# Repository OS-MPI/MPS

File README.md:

# The Magnetic Particle Spectroscopy (MPS) device
# [Link to the wiki](https://github.com/OS-MPI/MPS/wiki)
# [Link to the Main OS-MPI Page](https://os-mpi.github.io/)

## Motivation and Introduction

The system we are calling the MPS device is a low cost, and fairly simple to manufacture project which more generally speaking is a platform designed around understanding magnetic characteristics of superparamagentic iron oxide nanoparticles (SPIONs). The motivation was to condense the numerous existing systems into a singlular platform capable of providing insights into the nanoparticles irrespective of the specific goal of the lab. With that in mind, calling our platform an "MPS" system is rather imprecise; while one mode is traditional "spectroscopy" the device is designed to be flexible and able to perform relaxometry measurements as well as magnetometry, yet in order to give the project an easy-to-find, descriptive name, we settled on the "magnetic particle spectroscopy" system. 

## State of the project

In the current state (of March 2024) we have the system working in all [primary operational modes](https://github.com/OS-MPI/MPS/wiki/Modes-of-operation). It is capable of sensitively detecting SPIONs to the ng Fe level, quantifying the magnetization spectra, tracing the hysteresis loops, etc. 

The primary focus now is improving the documentation.

## System overview

Broadly speaking, there are four principle hardware components, the three coils (drive, receive, and bias) and the sample positioner. The drive coils produce magnetic fields (typ. 10 mT) which cause the SPIONs within the bore to go into and out of saturation at 23.8 kHz. This changing magnetism induces a voltage in the receive coils. The bias coils allow for the quasistatic operating point of the SPIONs to be modulated by generating low frequency (~10 Hz) fields up to about 50 mT.

### Drive/Transmit system
The drive system consists of the drive coils as well as the amplifier and filter. 

The drive coil is seen in the photograph above (the larger coil with four sub-sections). All of the four winding sections are in the same handedness. See the Wiki for further details. 

In this photograph, we utilize an in-house made Litz wire (18 strands of 28 AWG magnet wire), although other Litz wires may work similarly well. Previously a commercial Litz wire with 115 strands of 36AWG was used, but because of the plastic sleeve over the wires, they could not be easily stabilized with epoxy. 

The drive filter serves to purify and the waveform produced by the amplifier. Most amplifiers produce about 0.1% (or worse) total harmonic distortion, so without this filter those amplifier-generated distortions will dominate the noise floor. That being said, its among the most challenging components to manufacture, so its worth discussing which components are essential, and which are more or less optional. Refering to the schematic below, the two most important sections are the tuning/matching capacitors (C1 and C2), and the transformer (LPri and LSec). The tuning capacitors form a resonant circuit with Ldrive (the drive coil's equivalent load). This can be seen if you notice the loop formed by C1 C2 and LDrive is resonant. The choice of values for C1 and C2 is to make the equivalent impedance 8 ohms or so. The transformer should be a ferrite such as N87 and be designed such that the core flux is well below saturation (~20x lower, so 20ish mT). The purpose is to mitigate common-mode noise and provide isolation/break any ground loops. The other filter components can be "dropped in" later without disturbing the overall circuit. But these additional filtering components are both the most challenging to build, and less necessary. 

Many different drive amplifiers can be used. We have used both linear and switch-mode amplifiers with success. For a basic system, the AIYIMA A07 can be used, or other amplifiers based on the TPA3255 will likely be good choices. For example Nobsound G2 pro is also likely good and is pre-configured to be in PBTL mode. That IC from Texas Instruments has excellent performance given the cost and high switching frequency. The AE Techron 7224 is considerably more expensive, but produces a much higher fidelity waveform and has far more power available.

### Receive system

The receive system consists of the gradiometer receive coils, the filter, matching transformer, and preamplifier. The receive coil is a simple gradiometer to mitigate the net voltage induced from the changing magnetic drive fields (60-80 dBc attenuation of the voltage is a reasonable target). The filter reduces the amplitude of the signal at the drive frequency, but doesnt fully remove it. The matching transformer steps up the voltage produced by the receive coil (post filter) to improve the noise performance of the system. The transformer also provides isolation and common-mode supression, which help signal fidelity. The preamplifier amplifies the signal to a level more usable by the data acquisition hardware. In our case, we digitize the signals with a National Instruments NI PXIe 6363 and 6361. 

### Bias system

The bias system applies a low frequency (~10Hz), high amplitude waveform to probe the magnetization response at different quasistatic operating points. "Quasistatic" is emphasized here just because we utilize the assumption that this frequency is so low relaxation effects are negligible.

The system was initially designed to allow for even very small SPIONs (e.g. 5nm) to be probed out toward saturation, so many turns were added and cooling spaces were added to allow air to pass between the windings. With this design, passive convection is sufficient for normal operation at 50 mT peak. For up to 100 mT peak, lower duty cycles, or forced air should be used. 

This coil can be neglected if only hysteresis loop tracing or spectroscopy modes will be used. In that case, the diameter of the shielding tube should be increased to about 50-60 mm diameter. 

### Sample positioner

An automatic sample positioner is used to allow for consistent placement of the SPIONs as well as having the sample move in and out repeatedly to allow for multiple baselines to acquired. 

### Software

The software is written with LabVIEW 2021. Labview is not backwards compatible, so it must be operated with version 2021 or newer. 

With any issues regarding the project or missing files/documentation, [please reach out to the authors of this project here](https://github.com/OS-MPI/MPS/wiki/Contact-Us).

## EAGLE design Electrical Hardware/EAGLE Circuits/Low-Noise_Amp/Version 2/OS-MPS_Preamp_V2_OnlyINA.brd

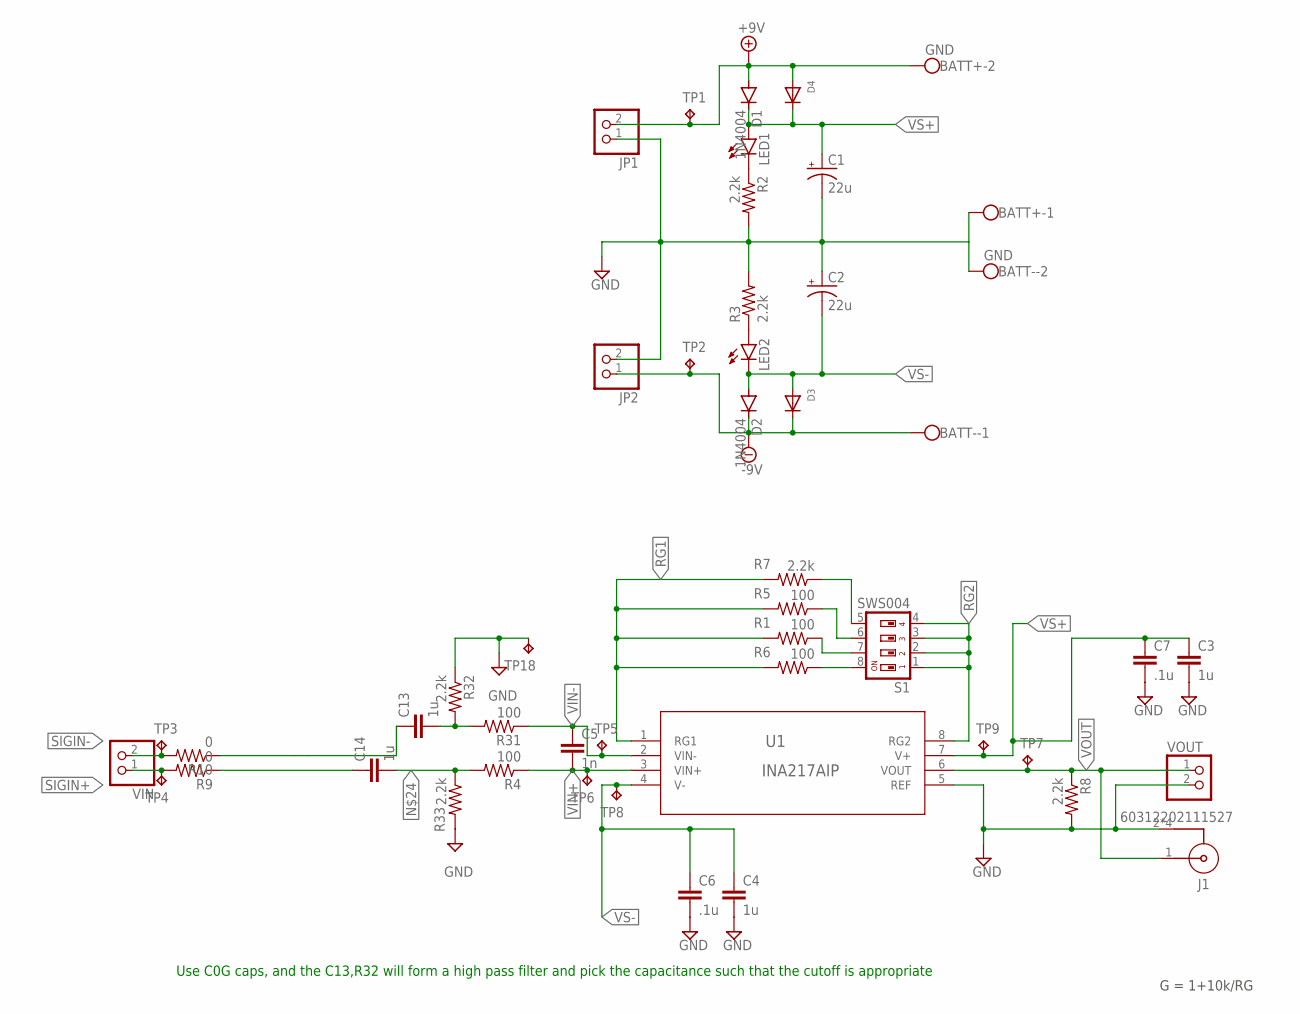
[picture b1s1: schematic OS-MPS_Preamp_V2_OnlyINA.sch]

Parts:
BATT+: GND; W237-102
BATT-: GND; W237-102
C1, C2: 22u; TT2D6
C3, C4, C13, C14: 1u; C1206
C5: 1n; C1206
C6, C7: .1u; C1206
D1, D2: 1N4004; DO41-10
D3, D4: DIODESOD-123; SOD-123
J1: 60312202111527
JP1, JP2: PINHD-1X2; 1X02
LED1, LED2: LEDSML0805; SML0805
R1, R4, R5, R6, R31: 100; R0805
R2, R3, R7, R8, R32, R33: 2.2k; R0805
R9, R10: 0; R0805
S1: SWS004; SMS-004
TP1, TP2: TPB2,54; B2,54
TP3, TP4, TP5, TP6, TP7, TP8, TP9, TP18: TPTP20SQ; TP20SQ
U1: INA217AIP; P8
VIN: PINHD-1X2; 1X02
VOUT: PINHD-1X2; 1X02

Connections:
+9V: BATT+.2, D1.A, D4.A, JP1.2, TP1.TP
-9V: BATT-.1, D2.C, D3.C, JP2.1, TP2.TP
GND: BATT+.1, BATT-.2, C1.-, C2.+, C3.2, C4.2, C6.2, C7.2, J1.2, J1.3 (2), J1.4 (2), J1.5 (2), JP1.1, JP2.2, R2.2, R3.2, R8.2, R32.1, R33.2, TP18.TP, U1.5 (REF), VOUT.2
unnamed: LED1.C, R2.1
unnamed: R5.1, S1.6
unnamed: R1.1, S1.7
unnamed: R6.1, S1.8
unnamed: R7.1, S1.5
unnamed: LED2.A, R3.1
unnamed: C13.1, R10.1
unnamed: C14.2, R4.2, R33.1
unnamed: C13.2, R31.2, R32.2
RG1: R1.2, R5.2, R6.2, R7.2, U1.1 (RG1)
RG2: S1.1, S1.2, S1.3, S1.4, U1.8 (RG2)
SIGIN+: R9.2, TP4.TP, VIN.1
SIGIN-: R10.2, TP3.TP, VIN.2
VIN+: C5.2, R4.1, TP6.TP, U1.3 (VIN+)
VIN+_1: C14.1, R9.1
VIN-: C5.1, R31.1, TP5.TP, U1.2 (VIN-)
VOUT: J1.1, R8.1, TP7.TP, U1.6 (VOUT), VOUT.1
VS+: C1.+, C3.1, C7.1, D1.C, D4.C, LED1.A, TP9.TP, U1.7 (V+)
VS-: C2.-, C4.1, C6.1, D2.A, D3.A, LED2.C, TP8.TP, U1.4 (V-)

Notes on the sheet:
Use C0G caps, and the C13,R32 will form a high pass filter and pick the capacitance such that the cutoff is appropriate
G = 1+10k/RG

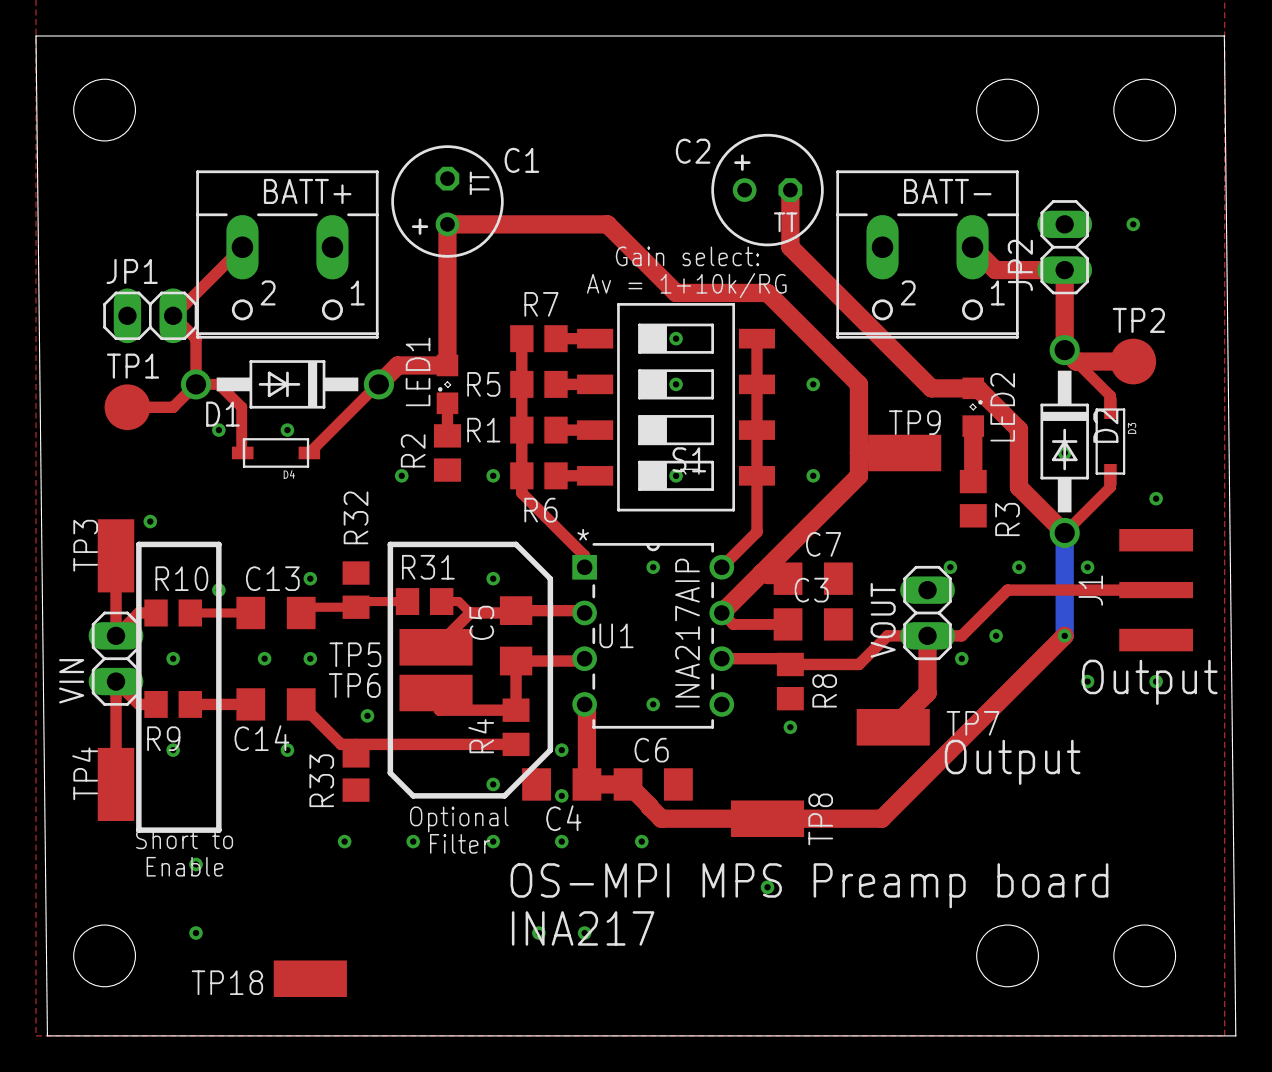
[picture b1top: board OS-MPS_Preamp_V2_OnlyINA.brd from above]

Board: 2 copper layers, 66.7 x 55.6 mm, 47 parts (0 on the bottom side), 22 nets.

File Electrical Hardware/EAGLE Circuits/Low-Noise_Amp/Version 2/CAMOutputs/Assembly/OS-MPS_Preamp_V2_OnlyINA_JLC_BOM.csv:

Comment,Designator,Package,LCSC Part,,,,,,,,,,,,,,,,,,,,,,2
2.2k,"R2,R3,R7,R8,R32,R33",R0805,C17520,,,,,,,,,,,,,,,,,,,,,,
0,"R9,R10",R0805,C17477,,,,,,,,,,,,,,,,,,,,,,
,"LED1,LED2",SML0805,C84256,,,,,,,,,,,,,,,,,,,,,,
100,"R1,R4,R5,R6,R31",R0805,C17408,,,,,,,,,,,,,,,,,,,,,,
,"D3,D4",SOD-123,C64898,,,,,,,,,,,,,,,,,,,,,,
100n,"C6,C7",C1206,C24497,,,,,,,,,,,,,,,,,,,,,,
1n,C5,C1206,C35216,,,,,,,,,,,,,,,,,,,,,,
SWS004,S1,SMS-004,C3693,,,,,,,,,,,,,,,,,,,,,,
1u,"C3,C4,C13,C14",C1206,C1848,,,,,,,,,,,,,,,,,,,,,,

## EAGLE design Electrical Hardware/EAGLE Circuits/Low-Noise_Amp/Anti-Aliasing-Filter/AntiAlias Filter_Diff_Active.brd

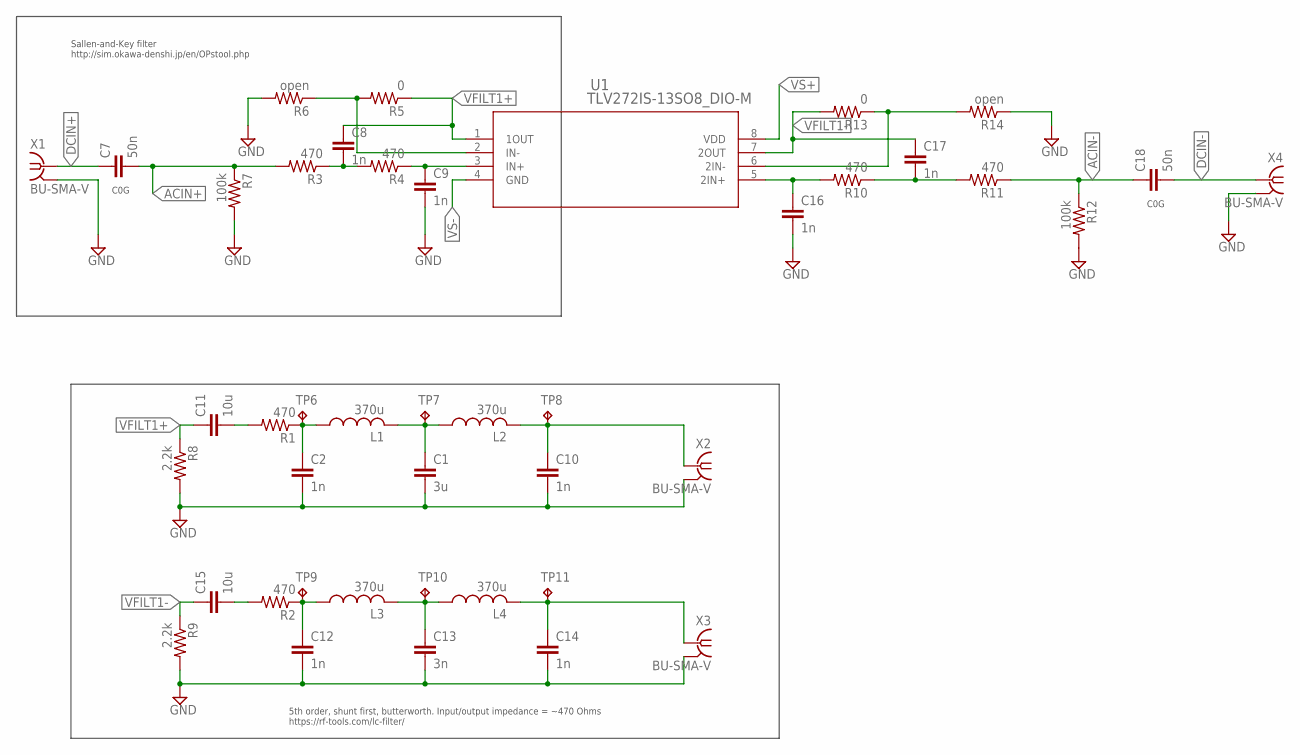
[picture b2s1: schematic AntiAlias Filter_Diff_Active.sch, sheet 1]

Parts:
C1: 3u; C1206
C2, C8, C9, C10, C12, C14, C16, C17: 1n; C1206
C7, C18: 50n; C1210
C11, C15: 10u; C1210
C13: 3n; C1206
L1, L2, L3, L4: 370u; L1812
R1, R2, R3, R4, R10, R11: 470; R1206
R5, R13: 0; R1206
R6, R14: open; R1206
R7, R12: 100k; R1206
R8, R9: 2.2k; R1206
TP6, TP7, TP8, TP9, TP10, TP11: TPTP20SQ; TP20SQ
U1: TLV272IS-13SO8_DIO-M; SO8_DIO-M
X1, X2, X3, X4: BU-SMA-V

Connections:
ACIN+: C7.2, R3.2, R7.1
ACIN-: C18.1, R11.1, R12.1
DCIN+: C7.1, X1.1
DCIN-: C18.2, X4.1
GND: C1.2, C2.2, C9.2, C10.2, C12.2, C13.2, C14.2, C16.2, R6.2, R7.2, R8.2, R9.2, R12.2, R14.1, X1.2, X1.3 (2), X1.4 (2), X1.5 (2), X2.2, X2.3 (2), X2.4 (2), X2.5 (2), X3.2, X3.3 (2), X3.4 (2), X3.5 (2), X4.2, X4.3 (2), X4.4 (2), X4.5 (2); also elsewhere on the board
unnamed: C2.1, L1.1, R1.1, TP6.TP
unnamed: C1.1, L1.2, L2.1, TP7.TP
unnamed: C11.2, R1.2
unnamed: C10.1, L2.2, TP8.TP, X2.1
unnamed: C14.1, L4.2, TP11.TP, X3.1
unnamed: C9.1, R4.1, U1.3 (IN+)
unnamed: C8.2, R3.1, R4.2
unnamed: R5.2, R6.1, U1.2 (IN-)
unnamed: C12.1, L3.1, R2.1, TP9.TP
unnamed: C13.1, L3.2, L4.1, TP10.TP
unnamed: C15.2, R2.2
unnamed: C17.2, R10.1, R11.2
unnamed: C16.1, R10.2, U1.5 (2IN+)
unnamed: R13.1, R14.2, U1.6 (2IN-)
VFILT1+: C8.1, C11.1, R5.1, R8.1, U1.1 (1OUT)
VFILT1-: C15.1, C17.1, R9.1, R13.2, U1.7 (2OUT)
VS+: U1.8 (VDD); also elsewhere on the board
VS-: U1.4 (GND); also elsewhere on the board

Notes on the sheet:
5th order, shunt first, butterworth. Input/output impedance = ~470 Ohms https://rf-tools.com/lc-filter/
Sallen-and-Key filter http://sim.okawa-denshi.jp/en/OPstool.php
C0G

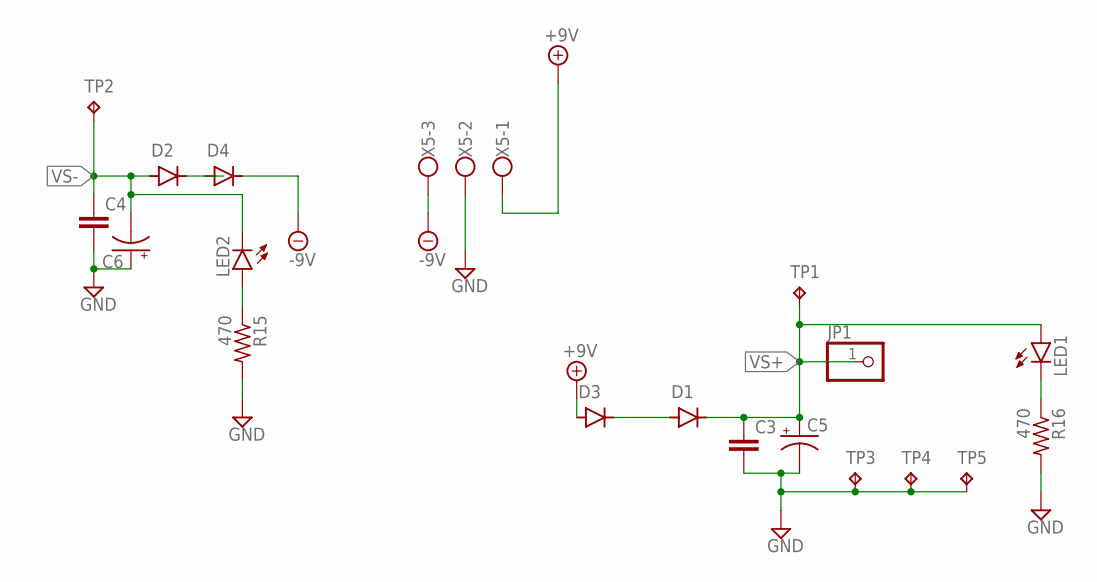
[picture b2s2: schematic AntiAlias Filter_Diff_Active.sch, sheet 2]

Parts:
C3, C4: C-EUC1206; C1206
C5, C6: CPOL-USE2.5-5; E2,5-5
D1, D2, D3, D4: DIODE-SMB; SMB
JP1: PINHD-1X1; 1X01
LED1, LED2: LEDCHIPLED_1206; CHIPLED_1206
R15, R16: 470; R1206
TP1, TP2, TP3, TP4, TP5: TPTP20SQ; TP20SQ
X5: W237-103

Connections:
+9V: D3.A, X5.1; also elsewhere on the board
-9V: D4.C, X5.3; also elsewhere on the board
GND: C3.2, C4.2, C5.-, C6.+, R15.2, R16.2, TP3.TP, TP4.TP, TP5.TP, X5.2; also elsewhere on the board
unnamed: LED2.A, R15.1
unnamed: LED1.C, R16.1
unnamed: D1.A, D3.C
unnamed: D2.C, D4.A
VS+: C3.1, C5.+, D1.C, JP1.1, LED1.A, TP1.TP; also elsewhere on the board
VS-: C4.1, C6.-, D2.A, LED2.C, TP2.TP; also elsewhere on the board

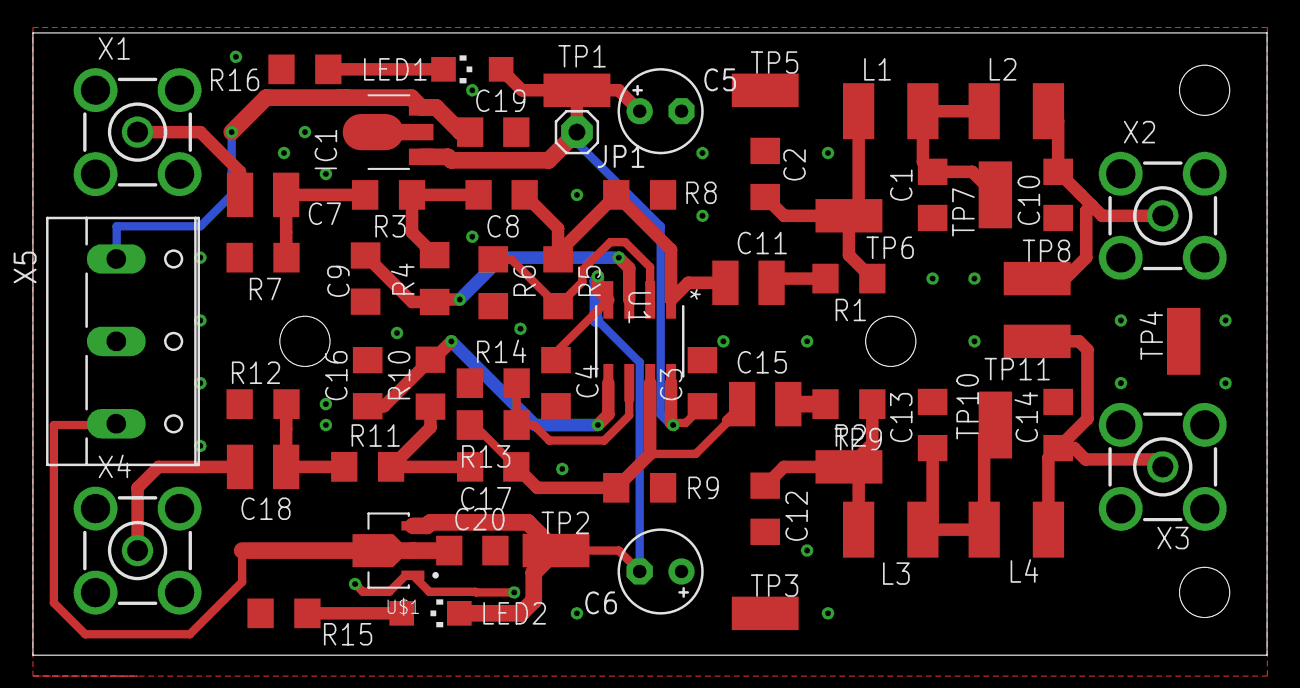
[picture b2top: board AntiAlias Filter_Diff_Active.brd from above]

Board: 2 copper layers, 74.9 x 37.8 mm, 62 parts (0 on the bottom side), 27 nets.

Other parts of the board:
C19, C20: C1206
IC1: 78L05F; SOT89
U$1: 79LXX; VREG_L78L12ABUTR

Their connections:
+9V: C19.1, IC1.3; also elsewhere on the board
-9V: C20.1, U$1.2; also elsewhere on the board
GND: C19.2, C20.2, IC1.2, IC1.2@1, U$1.1; also elsewhere on the board
VS+: IC1.1; also elsewhere on the board
VS-: U$1.3; also elsewhere on the board

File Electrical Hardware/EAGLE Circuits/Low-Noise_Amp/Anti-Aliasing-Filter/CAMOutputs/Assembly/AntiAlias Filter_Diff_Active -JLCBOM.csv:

Value,Designator,Package,LCSC Part
,"LED1, LED2",CHIPLED_1206,
10u,"C3, C4, C19, C20",C1206,
0,"R5, R13",R1206,
100k,"R7, R12",R1206,
10u,,C1210,
1n,"C2, C8, C9, C10, C12, C14, C16, C17",C1206,
2.2k,"R8, R9",R1206,
270u,"L1, L2, L3, L4",L1812,C394138
3n,"C1,C13",C1206,C141013
470,"R1, R2, R3, R4, R10, R11, R15, R16",R1206,
47n,"C7, C18,C11, C15",C1210,C342651
78L05F,IC1,SOT89,C181132
79LXX,U$1,SOT89,C122849
TLC082IDR,U1,SO8_DIO-M,C7710

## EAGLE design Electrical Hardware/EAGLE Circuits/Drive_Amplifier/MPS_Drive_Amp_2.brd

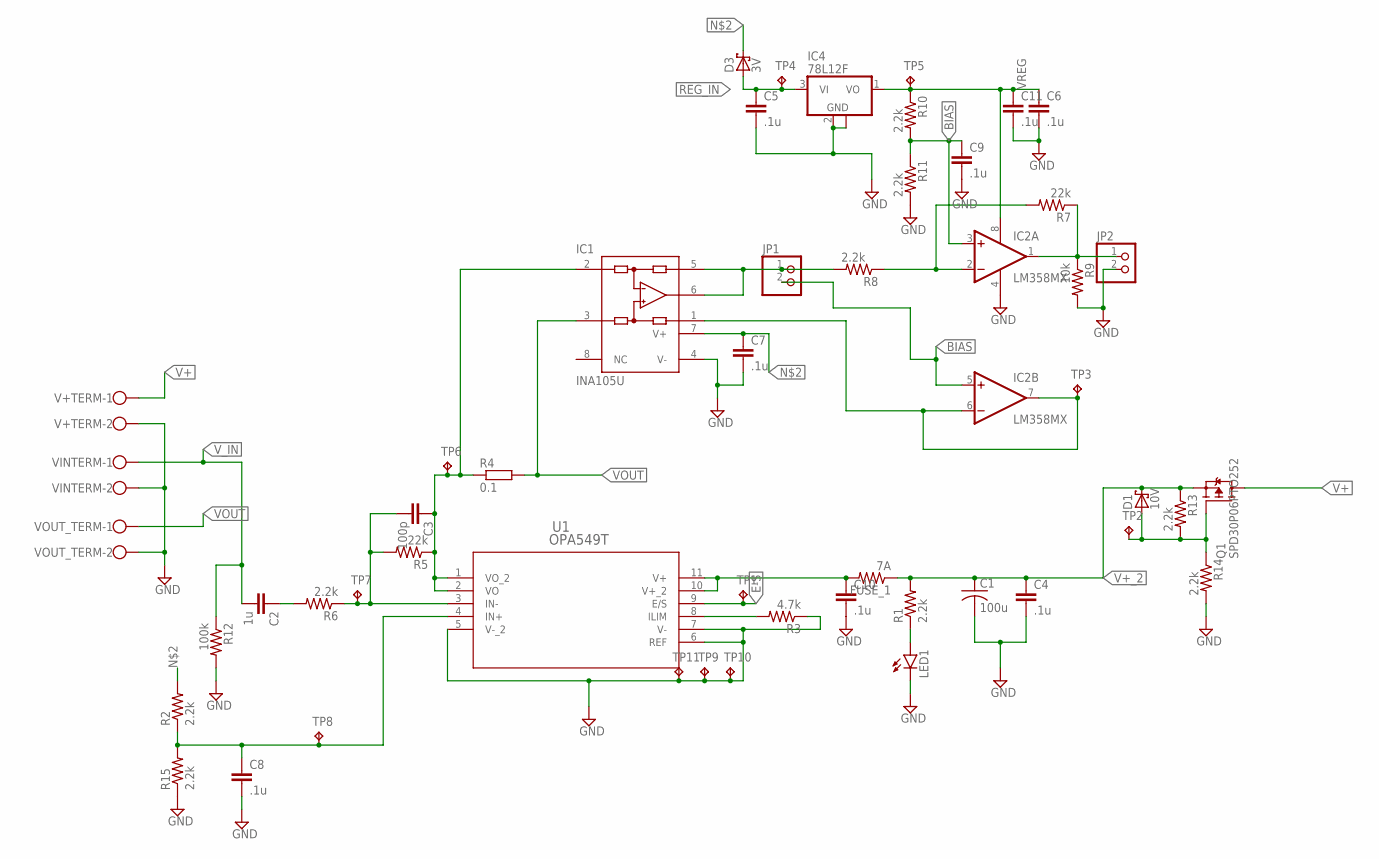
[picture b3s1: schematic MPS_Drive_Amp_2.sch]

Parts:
C1: 100u; C050-025X075
C2: 1u; C1206
C3: 100p; C1206
C4, C5, C6, C7, C8, C9, C10, C11: .1u; C1206
D1: 10V; DO35-7
D3: 3V; DO35-7
FUSE_1: 7A; R1206
IC1: INA105U; SO08
IC2: LM358MX; SO08
IC4: 78L12F; SOT89
JP1, JP2: PINHD-1X2; 1X02
LED1: LEDCHIPLED_0805; CHIPLED_0805
Q1: SPD30P06PTO252; TO252
R1, R2, R6, R8, R10, R11, R13, R14, R15: 2.2k; R1206
R3: 4.7k; R1206
R4: 0.1; VTA52
R5, R7: 22k; R1206
R9: 10k; R1206
R12: 100k; R1206
TP1, TP2, TP3, TP4, TP5, TP6, TP7, TP8, TP9, TP10, TP11: TPTP20SQ; TP20SQ
U1: OPA549T; KV11
V+TERM: W237-102
VINTERM: W237-102
VOUT_TERM: W237-102

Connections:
BIAS: C9.1, IC2.3 (+IN), IC2.5 (+IN), JP1.2, R10.2, R11.1
E-S: TP1.TP, U1.9 (E/S)
GND: C1.2, C4.2, C5.2, C6.2, C7.2, C8.2, C9.2, C10.2, C11.2, IC1.4 (V-), IC2.4 (V-), IC4.2 (GND), IC4.2@1 (GND), JP2.2, LED1.C, R3.1, R9.2, R11.2, R12.2, R14.2, R15.1, TP9.TP, TP10.TP, TP11.TP, U1.5 (V-_2), U1.6 (REF), U1.7 (V-), V+TERM.2, VINTERM.2, VOUT_TERM.2
unnamed: C3.1, IC1.2 (-IN), R4.1, R5.1, TP6.TP, U1.1 (VO_2), U1.2 (VO)
unnamed: C7.1, C10.1, D3.C, FUSE_1.2, IC1.7 (V+), R2.2, U1.10 (V+_2), U1.11 (V+)
unnamed: R3.2, U1.8 (ILIM)
unnamed: C2.1, R6.2
unnamed: LED1.A, R1.1
unnamed: C3.2, R5.2, R6.1, TP7.TP, U1.3 (IN-)
unnamed: IC1.5 (SENSE), IC1.6 (OUT), JP1.1, R8.2
unnamed: IC1.1 (REF), IC2.6 (-IN), IC2.7 (OUT), TP3.TP
unnamed: IC2.1 (OUT), JP2.1, R7.1, R9.1
unnamed: C8.1, R2.1, R15.2, TP8.TP, U1.4 (IN+)
unnamed: IC2.2 (-IN), R7.2, R8.1
PFET_GT: D1.A, Q1.1 (G), R13.2, R14.1, TP2.TP
REG_IN: C5.1, D3.A, IC4.3 (VI), TP4.TP
V+: Q1.3 (D), V+TERM.1
V+_2: C1.1, C4.1, D1.C, FUSE_1.1, Q1.2 (S), R1.2, R13.1
VOUT: IC1.3 (+IN), R4.2, VOUT_TERM.1
VREG: C6.1, C11.1, IC2.8 (V+), IC4.1 (VO), R10.1, TP5.TP
V_IN: C2.2, R12.1, VINTERM.1

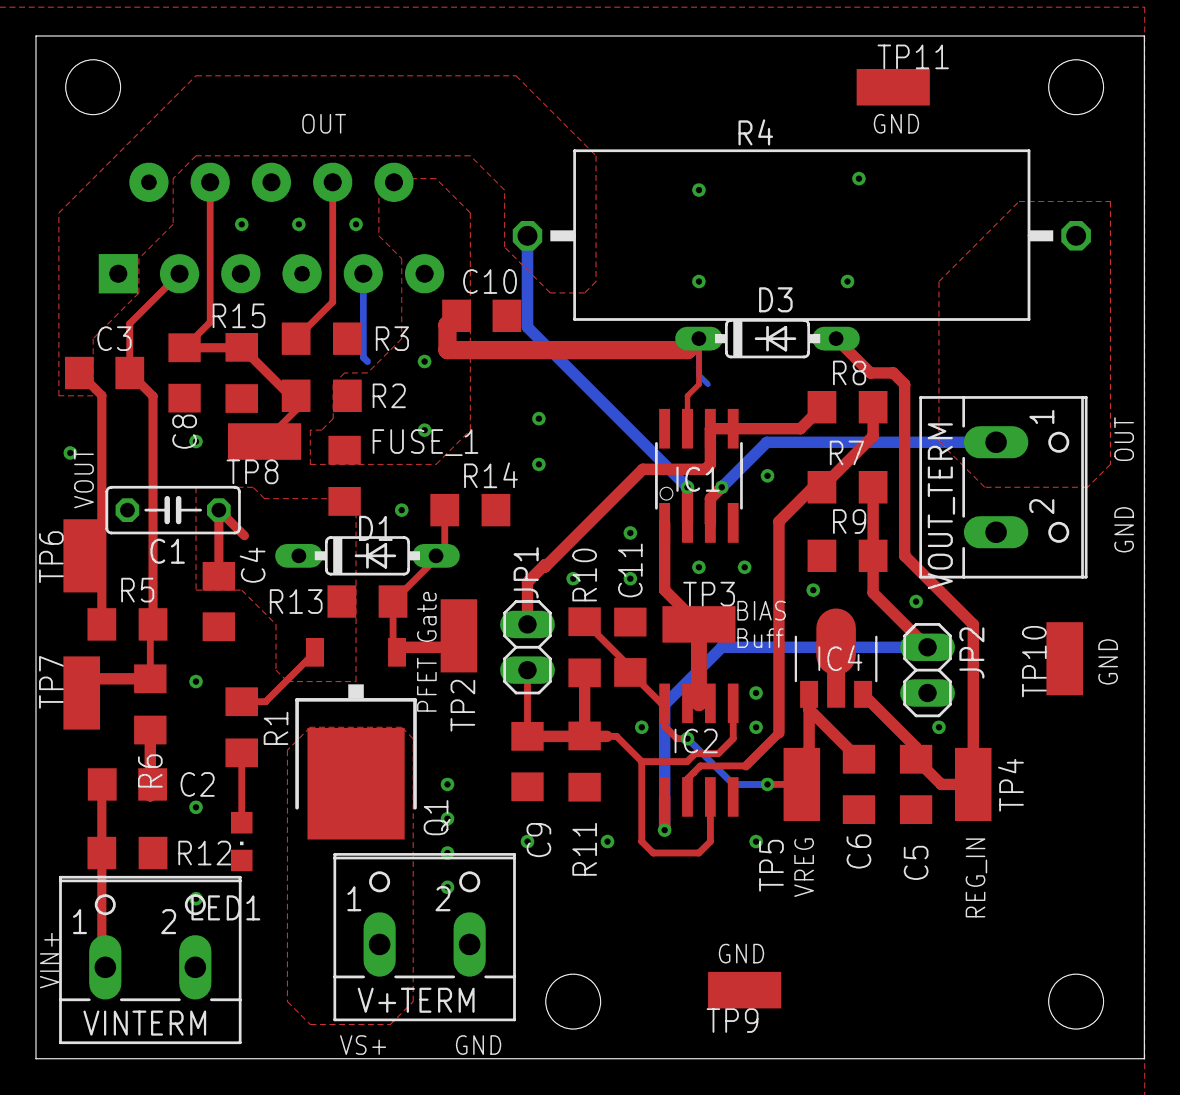
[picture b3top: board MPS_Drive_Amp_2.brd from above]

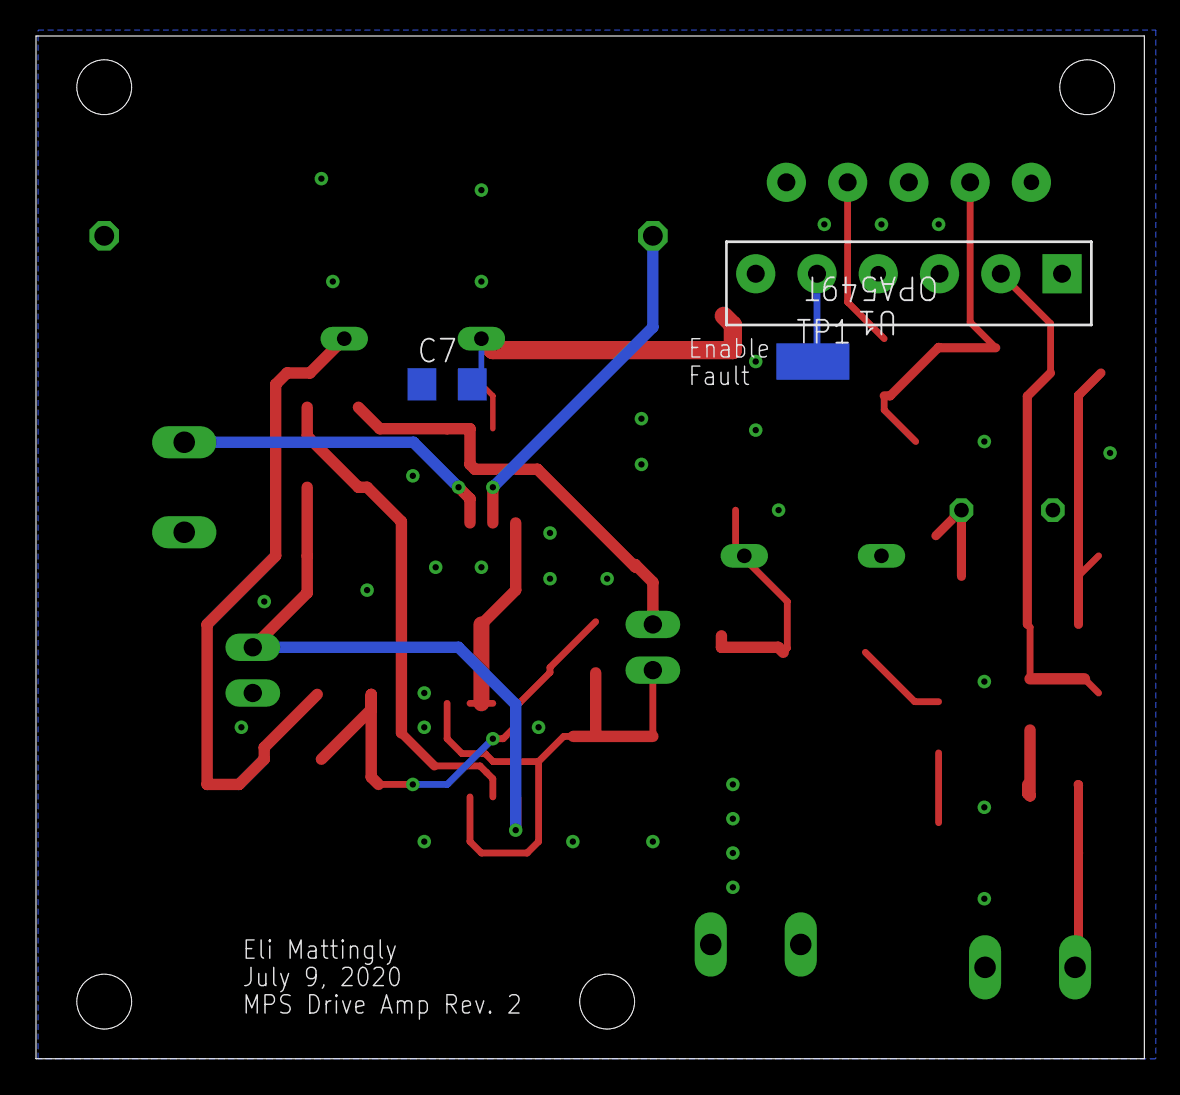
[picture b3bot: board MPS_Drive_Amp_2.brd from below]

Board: 2 copper layers, 61.6 x 56.8 mm, 51 parts (3 on the bottom side), 21 nets.

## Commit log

2019-12-01 Updatet_Part sheet
2019-12-02 Add Design Scripts
2020-02-17 Initial Inventor Part Push
2020-02-17 First MATLAB Script Push
2020-02-17 MATLAB Some Comments
    More commenting and cleaning code to come!
2020-02-17 Status Update README
2020-02-24 Updates and comments
2020-04-13 Update MATLAB Scripts
2020-07-22 Update Functions
2020-07-28 Update Scripts
2020-08-03 Update Many Scripts_ AddFullAnalysis
2020-08-03 Electrical Documentation
    Add LT Spice and PCB files
2020-08-04 Update TF Figure and ReadMe
2020-08-06 Update MATLAB
2020-08-14 Update Acquisition Scripts
2020-08-14 Add Example Data
2020-08-14 Update Composite Fig Function
2020-09-07 Update Scripts and BOM
2020-09-14 Update Inventor Files
2020-09-15 Update Inventor
2021-05-13 Add PCB BOM
    The BOM has been updated and PCB assembly files were added
2021-05-19 Version 2 initial update
    Initial update of files
2021-05-19 Update Inventor Part files
2021-05-20 Add Render and STEP file
2021-05-20 Update BOM for PreAmp
2021-06-06 Update Preamp Files
    Making them more compatible with fab.
2021-06-06 Update BOM/PnP
2021-07-07 Update sample holder+AA filter
2021-07-08 Update CAD
2021-07-08 Add STEP assembly
2021-07-08 PCB Pictures
2021-07-12 Update Bias optimization
2021-11-02 Add Comment
2021-11-02 Add KiCAD imported files
2022-04-08 Bulb Holders
2022-10-12 Filter Demo files
2022-10-12 New Drive coil FEMM
2022-11-01 Add results, update readme
2022-11-04 Reorganize files, archive old
2023-01-07 Inventor parts and labview
2023-01-07 Labview and Kicad
2023-01-16 Revert "Labview and Kicad"
    This reverts commit 51e892e73b62c1425be5d503678960fc262d96d0.
2023-01-16 Revert "Merge branch 'master' of https://github.com/OS-MPI/MPS"
    This reverts commit 0830b3b2eac63f10c73bfe72329d2da439e7747c, reversing
    changes made to c0ffb2e8f59d7c4befeacfec3356fb3a495e5a89.
2023-01-16 Demo Cross Section
2023-05-31 Inventor files
2023-07-01 Initialize Labview
2024-03-21 Move parts to archive
2024-03-21 Updated inventor files
2024-03-22 Update inventor assm

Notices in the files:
parts and their libraries:
Wurth_Connectors_WR-SMA: Copyright: Würth Elektronik
